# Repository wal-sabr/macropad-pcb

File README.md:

# macropad-pcb
Learning to make my own macropad PCB

Software used will be KiCad (because it's free)

Specs:
9 keys Macropad
May implement a rotary encoder in the future

Library:
Used these following libraries from ai03-2725

https://github.com/ai03-2725/MX_Alps_Hybrid

https://github.com/ai03-2725/random-keyboard-parts.pretty

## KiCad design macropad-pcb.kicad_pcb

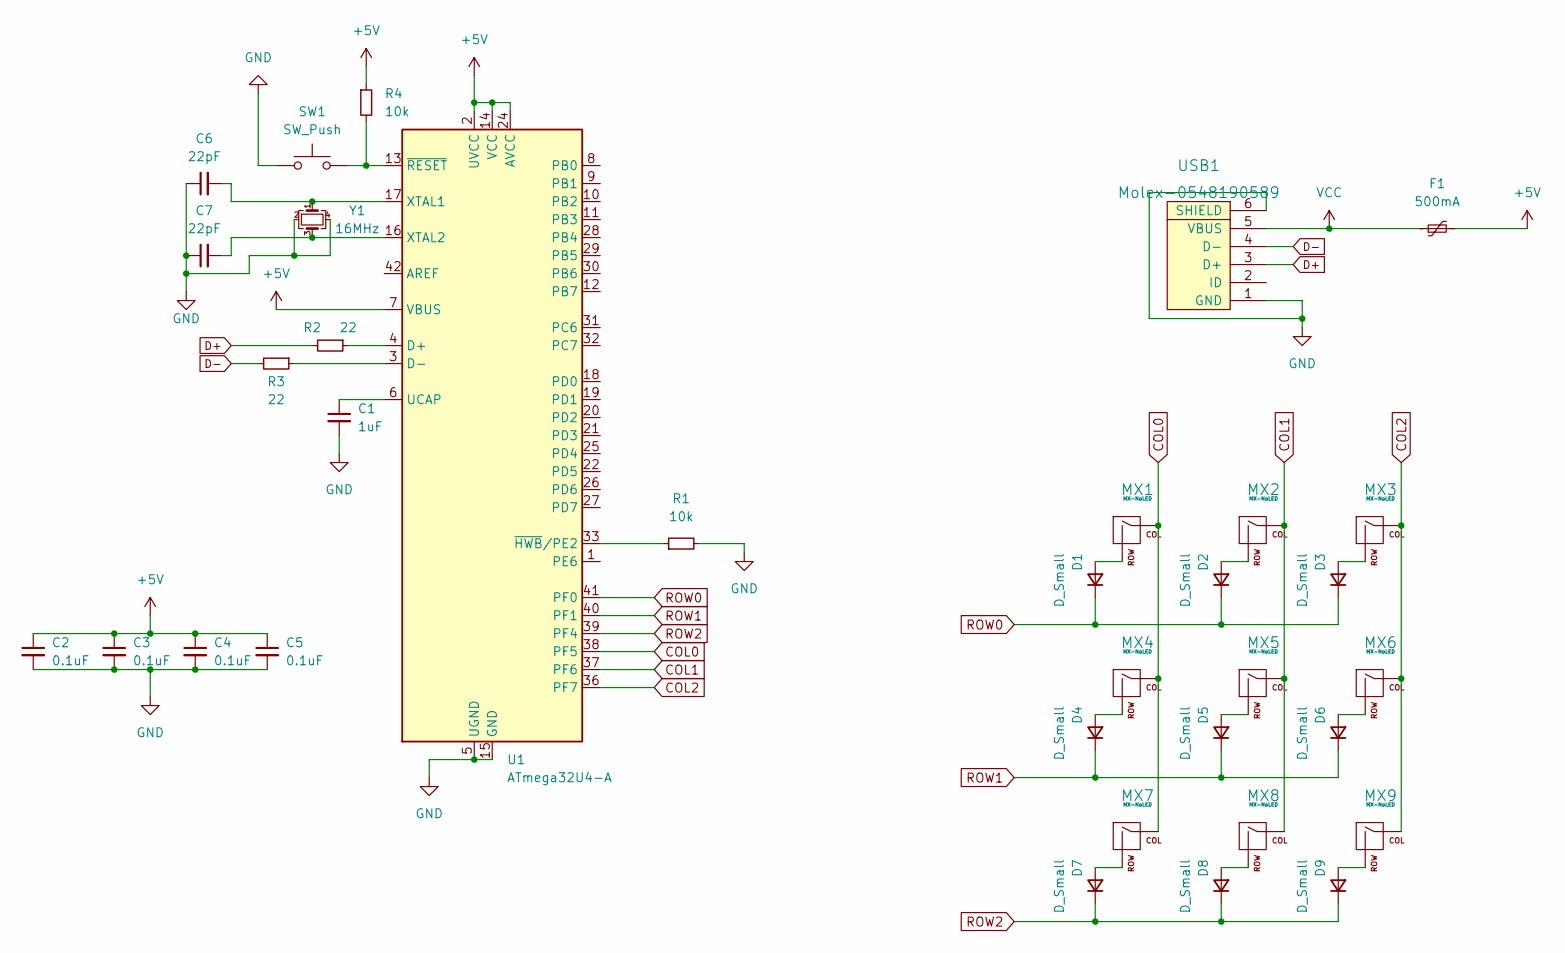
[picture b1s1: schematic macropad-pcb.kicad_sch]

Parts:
C1: 1uF; C_0805_2012Metric
C2, C3, C4, C5: 0.1uF; C_0805_2012Metric
C6, C7: 22pF; C_0805_2012Metric
D1, D2, D3, D4, D5, D6, D7, D8, D9: D_Small; D_SOD-123
F1: 500mA; Fuse_1206_3216Metric
MX1, MX2, MX3, MX4, MX5, MX6, MX7, MX8, MX9: MX-NoLED; MX-1U
R1, R4: 10k; R_0805_2012Metric
R2, R3: 22; R_0805_2012Metric
SW1: SW_Push; SKQG-1155865
U1: ATmega32U4-A; TQFP-44_10x10mm_P0.8mm
USB1: Molex-0548190589
Y1: 16MHz; Crystal_SMD_3225-4Pin_3.2x2.5mm

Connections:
+5V: C2.1, C3.1, C4.1, C5.1, F1.2, R4.1, U1.2 (UVCC), U1.7 (VBUS), U1.14 (VCC), U1.24 (AVCC), U1.34 (VCC), U1.44 (AVCC)
COL0: MX1.1 (COL), MX4.1 (COL), MX7.1 (COL), U1.38 (PF5)
COL1: MX2.1 (COL), MX5.1 (COL), MX8.1 (COL), U1.37 (PF6)
COL2: MX3.1 (COL), MX6.1 (COL), MX9.1 (COL), U1.36 (PF7)
D+: R2.2, USB1.3 (D+)
D-: R3.2, USB1.4 (D-)
GND: C1.2, C2.2, C3.2, C4.2, C5.2, C6.1, C7.1, R1.2, SW1.1, U1.5 (UGND), U1.15 (GND), U1.23 (GND), U1.35 (GND), U1.43 (GND), USB1.1 (GND), USB1.6 (SHIELD), Y1.2, Y1.4
unnamed: C1.1, U1.6 (UCAP)
unnamed: D1.2 (A), MX1.2 (ROW)
unnamed: D2.2 (A), MX2.2 (ROW)
unnamed: D3.2 (A), MX3.2 (ROW)
unnamed: D4.2 (A), MX4.2 (ROW)
unnamed: D5.2 (A), MX5.2 (ROW)
unnamed: D6.2 (A), MX6.2 (ROW)
unnamed: D7.2 (A), MX7.2 (ROW)
unnamed: D8.2 (A), MX8.2 (ROW)
unnamed: D9.2 (A), MX9.2 (ROW)
unnamed: R1.1, U1.33 (~HWB/PE2)
unnamed: R2.1, U1.4 (D+)
unnamed: R3.1, U1.3 (D-)
unnamed: R4.2, SW1.2, U1.13 (~RESET)
unnamed: C6.2, U1.17 (XTAL1), Y1.1
unnamed: C7.2, U1.16 (XTAL2), Y1.3
ROW0: D1.1 (K), D2.1 (K), D3.1 (K), U1.41 (PF0)
ROW1: D4.1 (K), D5.1 (K), D6.1 (K), U1.40 (PF1)
ROW2: D7.1 (K), D8.1 (K), D9.1 (K), U1.39 (PF4)
VCC: F1.1, USB1.5 (VBUS)

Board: 2 copper layers, 34 parts (22 on the bottom side), 27 nets, no tracks yet.

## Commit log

2021-12-31 edited the readme file
2021-12-31 adding PCB (KiCad) files
2021-12-31 Add submodules
2021-12-31 Adding Libraries
2021-12-31 Edited Readme file to include libraries used for KiCad
2021-12-31 minor edit
2021-12-31 minor minor edit
2022-01-01 Created a schematic on Microcontroller
2022-01-01 Making the PCB
2022-01-01 Did minor changes on pin assignment on the PCB
2022-04-12 Add submodules for Type-C library
2022-04-12 Add submodules for digikey-kicad-library library
